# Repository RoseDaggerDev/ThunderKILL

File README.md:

# ThunderKILL

ThunderKILL is based on the [Thundervolt](https://github.com/mackieks/thundervolt/tree/main) by [YveltalGriffin](https://github.com/mackieks) an open source platform for undervolting the Nintendo Wiis.
ThunderKILL takes the original concept and tries to go overkill with more features explicitly not inculded in the Thundervolt.
### New features:
- USB-C Power delivery
- Battery charge controller
- Fan and temperature controller
- RGB LED controller
- Current sensing
- 5V boost regulator
- E-Fuse on the PD power in
- Resettable fuse on the battery connection

### Existing features from Thundervolt:
- 1V buck regulator
- 1.15V buck regulator
- 1.8V buck regulator
- 3.3V buck boost regulator

All regulators are I2C controlled and high efficiency (η > 90%) and can be(/will be) controllable from a homebrew app. Along with the data from the I2C current/voltage/power sensing and temperature sensing of the board and the Wii.
The ThunderKILL has significantly more output pads than the original Thundervolt, as it is designed to integrate with other boards beyond the Wii itself, supplying easily available power, along with all the new features like PD negotiation, fan and LED outputs.

### ToDo:
- Final pass on board
- Send to printing
- Solder components
- Develop firmware
- Test in isolation
- Test on Wii
- Develop homebrew app

### NOTE: ThunderKILL is still in the prototype phase, and is untested, and the firmware for it has yet to be developed. I don’t recommend manufacturing ThunderKILL PCBs until development and testing are complete. This project is currently only for reference.

(This github page is still WIP, and will change as the project continues)

## Screenshots

## Credits

ThunderKILL hardware designed by [RoseDaggerDev](https://github.com/RoseDaggerDev)

Original Thundervolt credits:

Thundervolt hardware designed by [YveltalGriffin](https://github.com/mackieks)

Thundervolt firmware by [loopj ](https://github.com/loopj)

Thundervolt homebrew by:
- [YveltalGriffin](https://github.com/mackieks) (UI, app)
-  [loopj ](https://github.com/loopj) (I2C, app)
-  [Alex/supertazon](https://github.com/supertazon) (graphics)
-  [ShockSlayer ](https://github.com/ShockSlayer) (music)

## License

ThunderKILL hardware is licensed under Solderpad Hardware License v2.1.

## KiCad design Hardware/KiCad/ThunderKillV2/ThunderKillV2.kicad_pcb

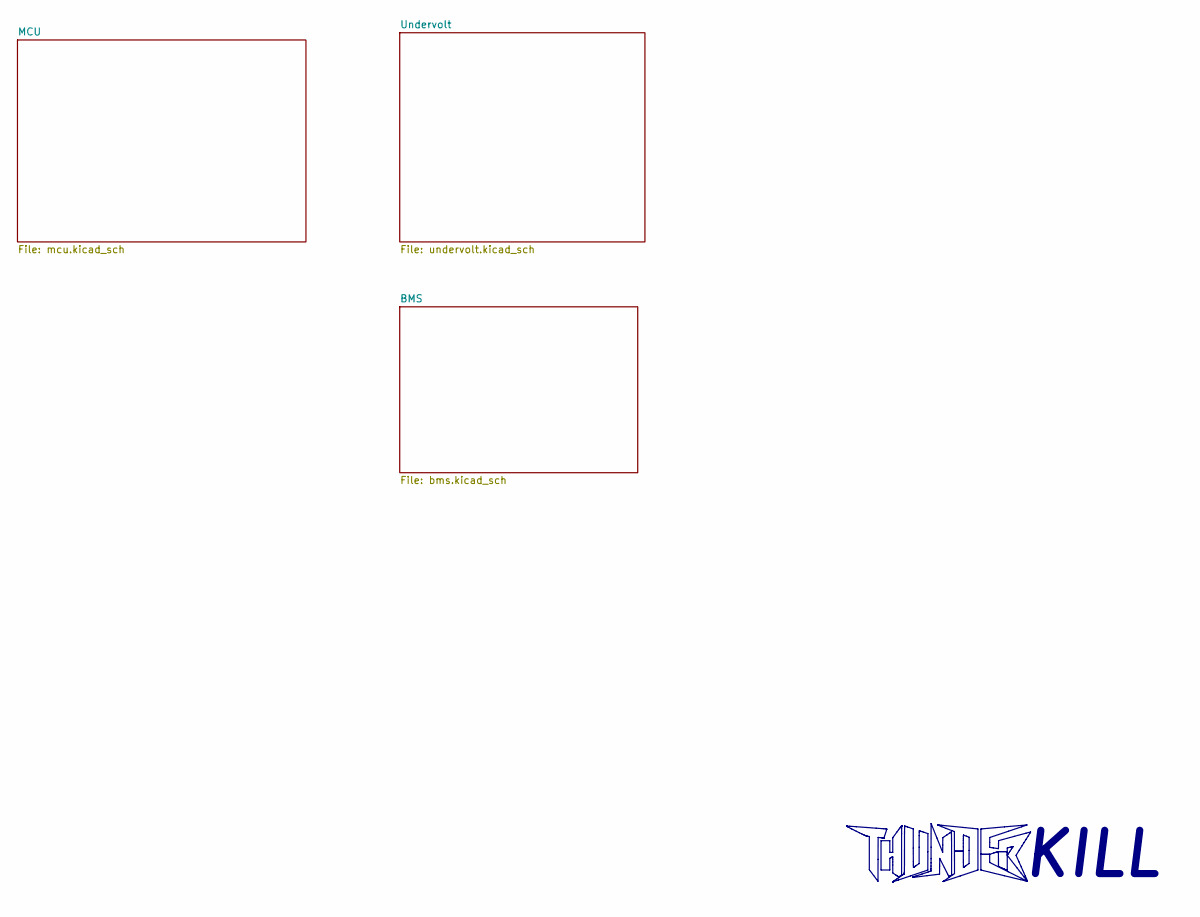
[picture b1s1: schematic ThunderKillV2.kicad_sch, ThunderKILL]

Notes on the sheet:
KILL

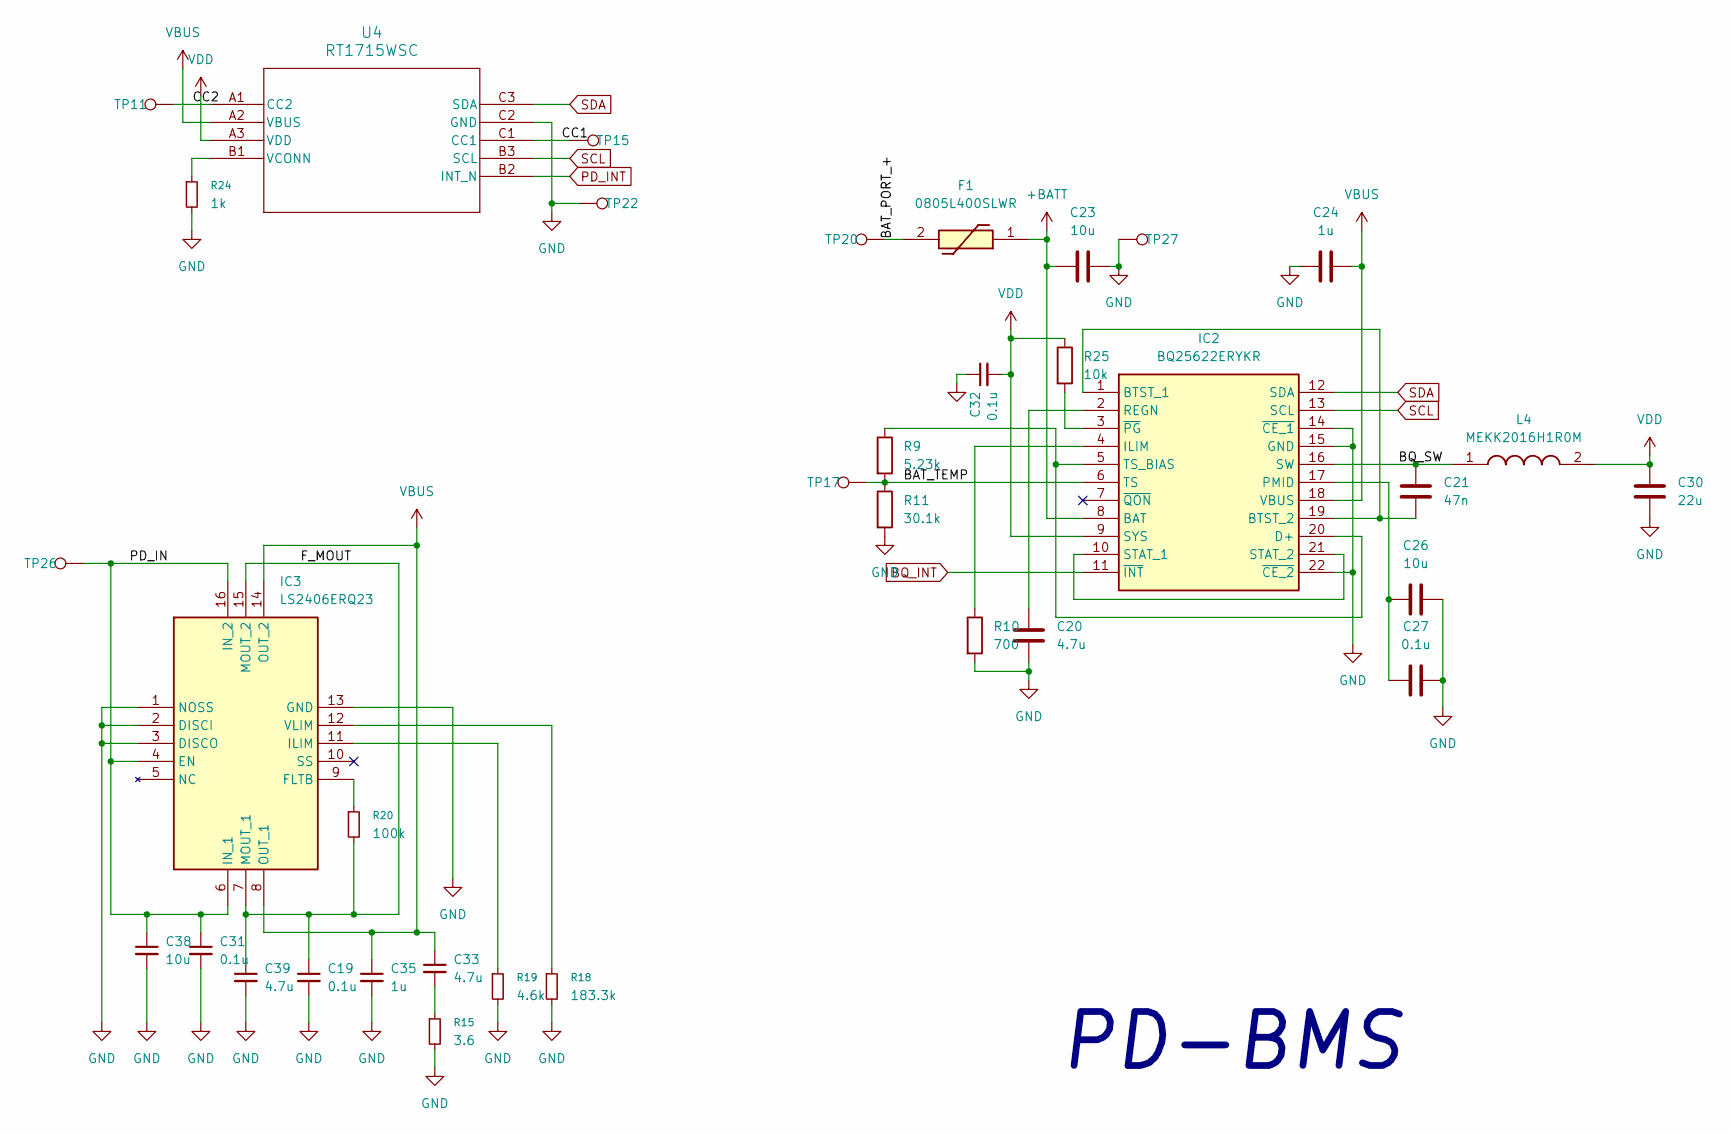
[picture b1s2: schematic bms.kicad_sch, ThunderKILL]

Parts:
C19, C27, C31, C32: 0.1u; C_0402_1005Metric; Manufacturer_Part_Number GCM155R71H104KE02J; Digi-Key Part # 490-14514-1-ND
C20, C33, C39: 4.7u; C_0402_1005Metric; Manufacturer_Part_Number GRM155C61E475ME15J; Digi-Key Part # 490-GRM155C61E475ME15JCT-ND
C21: 47n; C_0402_1005Metric; Manufacturer_Part_Number GRM155R71H473KE14D; Digi-Key Part # 490-10702-1-ND
C23, C26, C38: 10u; C_0603_1608Metric; Manufacturer_Part_Number GRM188R61E106KA73D; Digi-Key Part # 490-18214-1-ND
C24, C35: 1u; C_0402_1005Metric; Manufacturer_Part_Number GRM155R61E105KA12D; Digi-Key Part # 490-10017-1-ND
C30: 22u; C_0603_1608Metric; Manufacturer_Part_Number GRM188C61E226ME01W; Digi-Key Part # 490-GRM188C61E226ME01WCT-ND
F1: 0805L400SLWR; 0805L075SLYR; Mouser Part Number 576-0805L400SLWR
IC2: BQ25622ERYKR; Mouser Part Number 595-BQ25622ERYKR
IC3: LS2406ERQ23; Mouser Part Number 576-LS2406ERQ23
L4: MEKK2016H1R0M; INDPM2016X100N; Mouser Part Number 963-MEKK2016H1R0M
R9: 5.23k; R_0402_1005Metric; Manufacturer_Part_Number RMCF0402FT5K23; Digi-Key Part # RMCF0402FT5K23CT-ND
R10: 700; R_0402_1005Metric; Manufacturer_Part_Number RMCF0402FT698R; Digi-Key Part # RMCF0402FT698RCT-ND
R11: 30.1k; R_0402_1005Metric; Manufacturer_Part_Number RMCF0402FT30K1; Digi-Key Part # RMCF0402FT30K1CT-ND
R15: 3.6; R_0402_1005Metric; Manufacturer_Part_Number RMCF0402FT3R60; Digi-Key Part # RMCF0402FT3R60CT-ND
R18: 183.3k; R_0402_1005Metric; Manufacturer_Part_Number RMCF0402FT182K; Digi-Key Part # RMCF0402FT182KCT-ND
R19: 4.6k; R_0402_1005Metric; Manufacturer_Part_Number RMCF0402FT4K64; Digi-Key Part # RMCF0402FT4K64CT-ND
R20: 100k; R_0402_1005Metric; Manufacturer_Part_Number CRCW0402100KFKED; Digi-Key Part # 541-100KLCT-ND
R24: 1k; R_0402_1005Metric; Manufacturer_Part_Number CRCW04021K00FKED; Digi-Key Part # 541-1.00KLCT-ND
R25: 10k; R_0402_1005Metric; Manufacturer_Part_Number CRCW040210K0FKED; Digi-Key Part # 541-10.0KLCT-ND
TP11: CC2; TestPoint_Pad_D1.0mm
TP15: CC1; TestPoint_Pad_D1.0mm
TP17: BAT_TMP; TestPoint_Pad_D1.0mm
TP20: BAT+; TestPoint_Pad_3x1.0mm
TP22: GND; TestPoint_Pad_3x1.0mm
TP26: VBUS; TestPoint_Pad_3x1.0mm
TP27: BAT-; TestPoint_Pad_3x1.0mm
U4: RT1715WSC; BGA3X3_RT1715WSC_RIT; Manufacturer_Part_Number RT1715WSC; Digi-Key Part # RT1715WSCCT-ND

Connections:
+BATT: C23.1, F1.1, IC2.8 (BAT)
/BMS/BAT_PORT_+: F1.2, TP20.1
/BMS/BAT_TEMP: IC2.6 (TS), R9.2, R11.1, TP17.1
/BMS/BQ_SW: C21.1, IC2.16 (SW), L4.1
/BMS/CC1: TP15.1, U4.C1 (CC1)
/BMS/CC2: TP11.1, U4.A1 (CC2)
/BMS/F_MOUT: C19.1, C39.1, IC3.7 (MOUT_1), IC3.15 (MOUT_2), R20.2
/BMS/PD_IN: C31.1, C38.1, IC3.4 (EN), IC3.6 (IN_1), IC3.16 (IN_2), TP26.1
BQ_INT: IC2.11 (~INT); also elsewhere on the board
GND: C19.2, C20.2, C23.2, C24.1, C26.2, C27.2, C30.2, C31.2, C32.1, C35.2, C38.2, C39.2, IC2.14 (~CE_1), IC2.15 (GND), IC2.22 (~CE_2), IC3.1 (NOSS), IC3.2 (DISCI), IC3.3 (DISCO), IC3.13 (GND), R10.2, R11.2, R15.2, R18.2, R19.2, R24.2, TP22.1, TP27.1, U4.C2 (GND); also elsewhere on the board
unnamed: C33.2, R15.1
unnamed: C21.2, IC2.1 (BTST_1), IC2.19 (BTST_2)
unnamed: IC2.5 (TS_BIAS), IC2.20 (D+), R9.1
unnamed: IC2.4 (ILIM), R10.1
unnamed: C26.1, C27.1, IC2.17 (PMID)
unnamed: C20.1, IC2.2 (REGN)
unnamed: IC2.10 (STAT_1), IC2.21 (STAT_2)
unnamed: IC2.3 (~PG), R25.2
unnamed: IC3.9 (FLTB), R20.1
unnamed: IC3.11 (ILIM), R19.1
unnamed: IC3.12 (VLIM), R18.1
unnamed: R24.1, U4.B1 (VCONN)
PD_INT: U4.B2 (INT_N); also elsewhere on the board
SCL: IC2.13 (SCL), U4.B3 (SCL); also elsewhere on the board
SDA: IC2.12 (SDA), U4.C3 (SDA); also elsewhere on the board
VBUS: C24.2, C33.1, C35.1, IC2.18 (VBUS), IC3.8 (OUT_1), IC3.14 (OUT_2), U4.A2 (VBUS)
VDD: C30.1, C32.2, IC2.9 (SYS), L4.2, R25.1, U4.A3 (VDD); also elsewhere on the board

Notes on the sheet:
PD-BMS

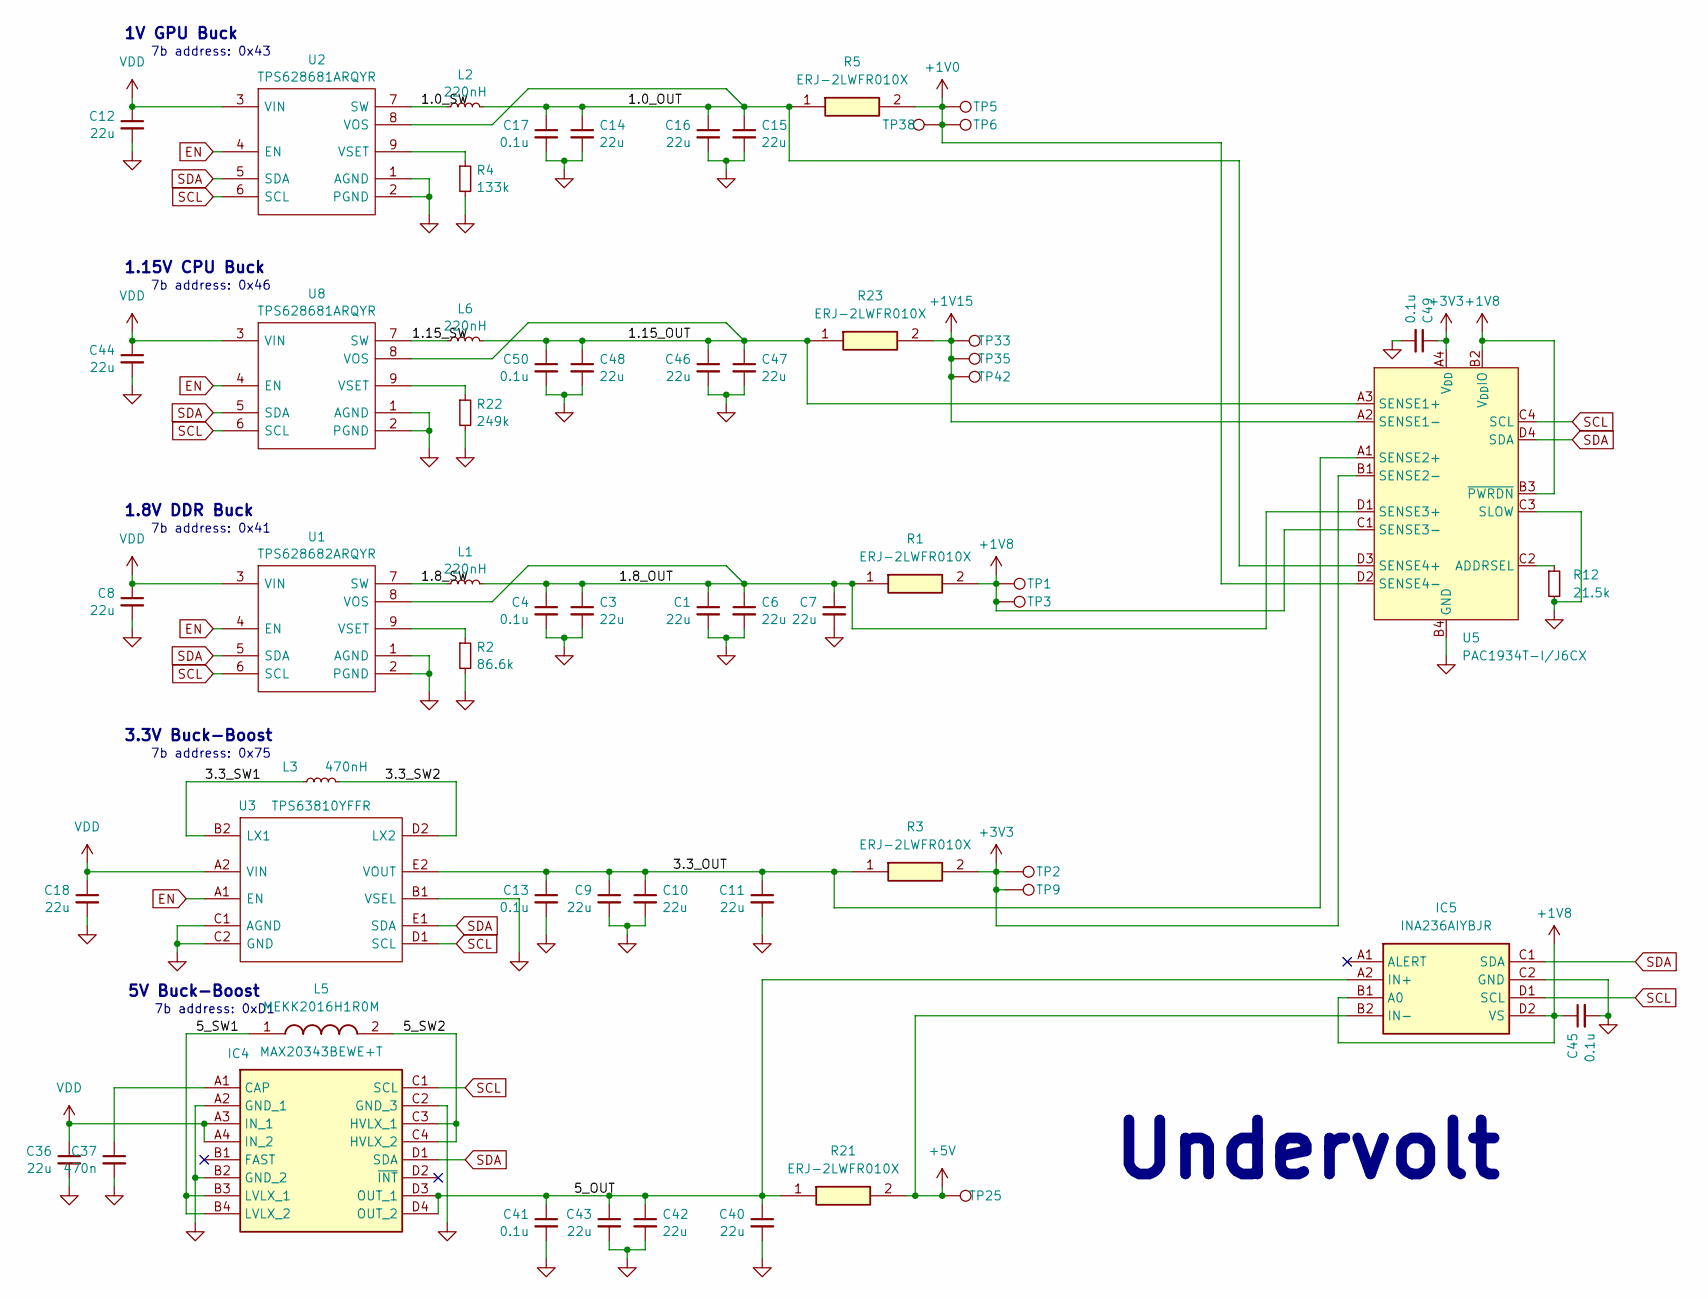
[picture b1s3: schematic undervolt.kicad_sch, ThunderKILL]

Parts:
C1, C3, C6, C7, C8, C9, C10, C11, C12, C14, C15, C16, C18, C36, C40, C42, C43, C44, C46, C47, C48: 22u; C_0603_1608Metric; Manufacturer_Part_Number GRM188C61E226ME01W; Digi-Key Part # 490-GRM188C61E226ME01WCT-ND
C4, C13, C17, C41, C45, C49, C50: 0.1u; C_0402_1005Metric; Manufacturer_Part_Number GCM155R71H104KE02J; Digi-Key Part # 490-14514-1-ND
C37: 470n; C_0402_1005Metric; Manufacturer_Part_Number GRM155R61E105KA12D; Digi-Key Part # 490-10017-1-ND
IC4: MAX20343BEWE+T; BGA16C40P4X4_201X177X69; Mouser Part Number 700-MAX20343BEWE+T
IC5: INA236AIYBJR; BGA8C40P2X4_70X147X35; Mouser Part Number 595-INA236AIYBJR
L1, L2, L6: 220nH; INDPM4442X150N; Manufacturer_Part_Number MPI4015V2-R22-R; Digi-Key Part # 283-MPI4015V2-R22-RCT-ND
L3: 470nH; L_0805_2012Metric; Manufacturer_Part_Number TFM201208BLE-R47MTCF; Digi-Key Part # 445-TFM201208BLE-R47MTCFCT-ND
L5: MEKK2016H1R0M; INDPM2016X100N; Mouser Part Number 963-MEKK2016H1R0M
R1, R3, R5, R21, R23: ERJ-2LWFR010X; R_0402_1005Metric; Mouser Part Number 667-ERJ-2LWFR010X
R2: 86.6k; R_0402_1005Metric; Manufacturer_Part_Number RMCF0402FT86K6; Digi-Key Part # RMCF0402FT86K6CT-ND
R4: 133k; R_0402_1005Metric; Manufacturer_Part_Number RMCF0402FT133K; Digi-Key Part # RMCF0402FT133KCT-ND
R12: 21.5k; R_0402_1005Metric; Manufacturer_Part_Number RMCF0402FT3R60; Digi-Key Part # RMCF0402FT3R60CT-ND
R22: 249k; R_0402_1005Metric; Manufacturer_Part_Number CRCW0402249KFKED; Digi-Key Part # 541-249KLCT-ND
TP1, TP3: 1V8; TestPoint_Pad_3x1.0mm
TP2: 3V3; TestPoint_Pad_1.5x1.0mm
TP5, TP6, TP38: 1V0; TestPoint_Pad_3x1.0mm
TP9: 3V3; TestPoint_Pad_3x1.0mm
TP25: 5V; TestPoint_Pad_3x1.0mm
TP33, TP35, TP42: 1V15; TestPoint_Pad_3x1.0mm
U1: TPS628682ARQYR; TPS628680ARQYR; Mouser Part Number 595-TPS628682ARQYR
U2, U8: TPS628681ARQYR; TPS628680ARQYR; Mouser Part Number 595-TPS628681ARQYR
U3: TPS63810YFFR; BGA15C40P3X5_134X226X62; Mouser Part Number 595-TPS63810YFFR
U5: PAC1934T-I/J6CX; WLCSP-16_2.225x2.17mm_Layout4x4_P0.5mm; Manufacturer_Part_Number PAC1934T-I/J6CX; Digi-Key Part # PAC1934T-I/J6CX-CT-ND

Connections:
+1V0: R5.2, TP5.1, TP6.1, TP38.1, U5.D2 (SENSE4-)
+1V8: C45.1, IC5.B1 (A0), IC5.D2 (VS), R1.2, TP1.1, TP3.1, U5.B2 (V_{DD}IO), U5.B3 (~PWRDN), U5.C1 (SENSE3-); also elsewhere on the board
+1V15: R23.2, TP33.1, TP35.1, TP42.1, U5.A2 (SENSE1-)
+3V3: C49.1, R3.2, TP2.1, TP9.1, U5.A4 (V_{DD}), U5.B1 (SENSE2-); also elsewhere on the board
+5V: IC5.B2 (IN-), R21.2, TP25.1
/Undervolt/1.0_OUT: C14.1, C15.1, C16.1, C17.1, L2.2, R5.1, U2.8 (VOS), U5.D3 (SENSE4+)
/Undervolt/1.0_SW: L2.1, U2.7 (SW)
/Undervolt/1.8_OUT: C1.1, C3.1, C4.1, C6.1, C7.1, L1.2, R1.1, U1.8 (VOS), U5.D1 (SENSE3+)
/Undervolt/1.8_SW: L1.1, U1.7 (SW)
/Undervolt/1.15_OUT: C46.1, C47.1, C48.1, C50.1, L6.2, R23.1, U5.A3 (SENSE1+), U8.8 (VOS)
/Undervolt/1.15_SW: L6.1, U8.7 (SW)
/Undervolt/3.3_OUT: C9.1, C10.1, C11.1, C13.1, R3.1, U3.E2 (VOUT), U3.E3 (VOUT_2), U5.A1 (SENSE2+)
/Undervolt/3.3_SW1: L3.1, U3.B2 (LX1), U3.B3 (LX1_2)
/Undervolt/3.3_SW2: L3.2, U3.D2 (LX2), U3.D3 (LX2_2)
/Undervolt/5_OUT: C40.1, C41.1, C42.1, C43.1, IC4.D3 (OUT_1), IC4.D4 (OUT_2), IC5.A2 (IN+), R21.1
/Undervolt/5_SW1: IC4.B3 (LVLX_1), IC4.B4 (LVLX_2), L5.1
/Undervolt/5_SW2: IC4.C3 (HVLX_1), IC4.C4 (HVLX_2), L5.2
EN: U1.4 (EN), U2.4 (EN), U3.A1 (EN), U8.4 (EN); also elsewhere on the board
GND: C1.2, C3.2, C4.2, C6.2, C7.2, C8.2, C9.2, C10.2, C11.2, C12.2, C13.2, C14.2, C15.2, C16.2, C17.2, C18.2, C36.2, C37.2, C40.2, C41.2, C42.2, C43.2, C44.2, C45.2, C46.2, C47.2, C48.2, C49.2, C50.2, IC4.A2 (GND_1), IC4.B2 (GND_2), IC4.C2 (GND_3), IC5.C2 (GND), R2.2, R4.2, R12.2, R22.2, U1.1 (AGND), U1.2 (PGND), U2.1 (AGND), U2.2 (PGND), U3.B1 (VSEL), U3.C1 (AGND), U3.C2 (GND), U3.C3 (GND_2), U5.B4 (GND), U5.C3 (SLOW), U8.1 (AGND), U8.2 (PGND); also elsewhere on the board
unnamed: C37.1, IC4.A1 (CAP)
unnamed: R2.1, U1.9 (VSET)
unnamed: R4.1, U2.9 (VSET)
unnamed: R12.1, U5.C2 (ADDRSEL)
unnamed: R22.1, U8.9 (VSET)
SCL: IC4.C1 (SCL), IC5.D1 (SCL), U1.6 (SCL), U2.6 (SCL), U3.D1 (SCL), U5.C4 (SCL), U8.6 (SCL); also elsewhere on the board
SDA: IC4.D1 (SDA), IC5.C1 (SDA), U1.5 (SDA), U2.5 (SDA), U3.E1 (SDA), U5.D4 (SDA), U8.5 (SDA); also elsewhere on the board
VDD: C8.1, C12.1, C18.1, C36.1, C44.1, IC4.A3 (IN_1), IC4.A4 (IN_2), U1.3 (VIN), U2.3 (VIN), U3.A2 (VIN), U3.A3 (VIN_2), U8.3 (VIN); also elsewhere on the board

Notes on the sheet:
1.8V DDR Buck
7b address: 0x75
3.3V Buck-Boost
1.15V CPU Buck
7b address: 0x43
7b address: 0xD1
7b address: 0x41
1V GPU Buck
Undervolt
5V Buck-Boost
7b address: 0x46

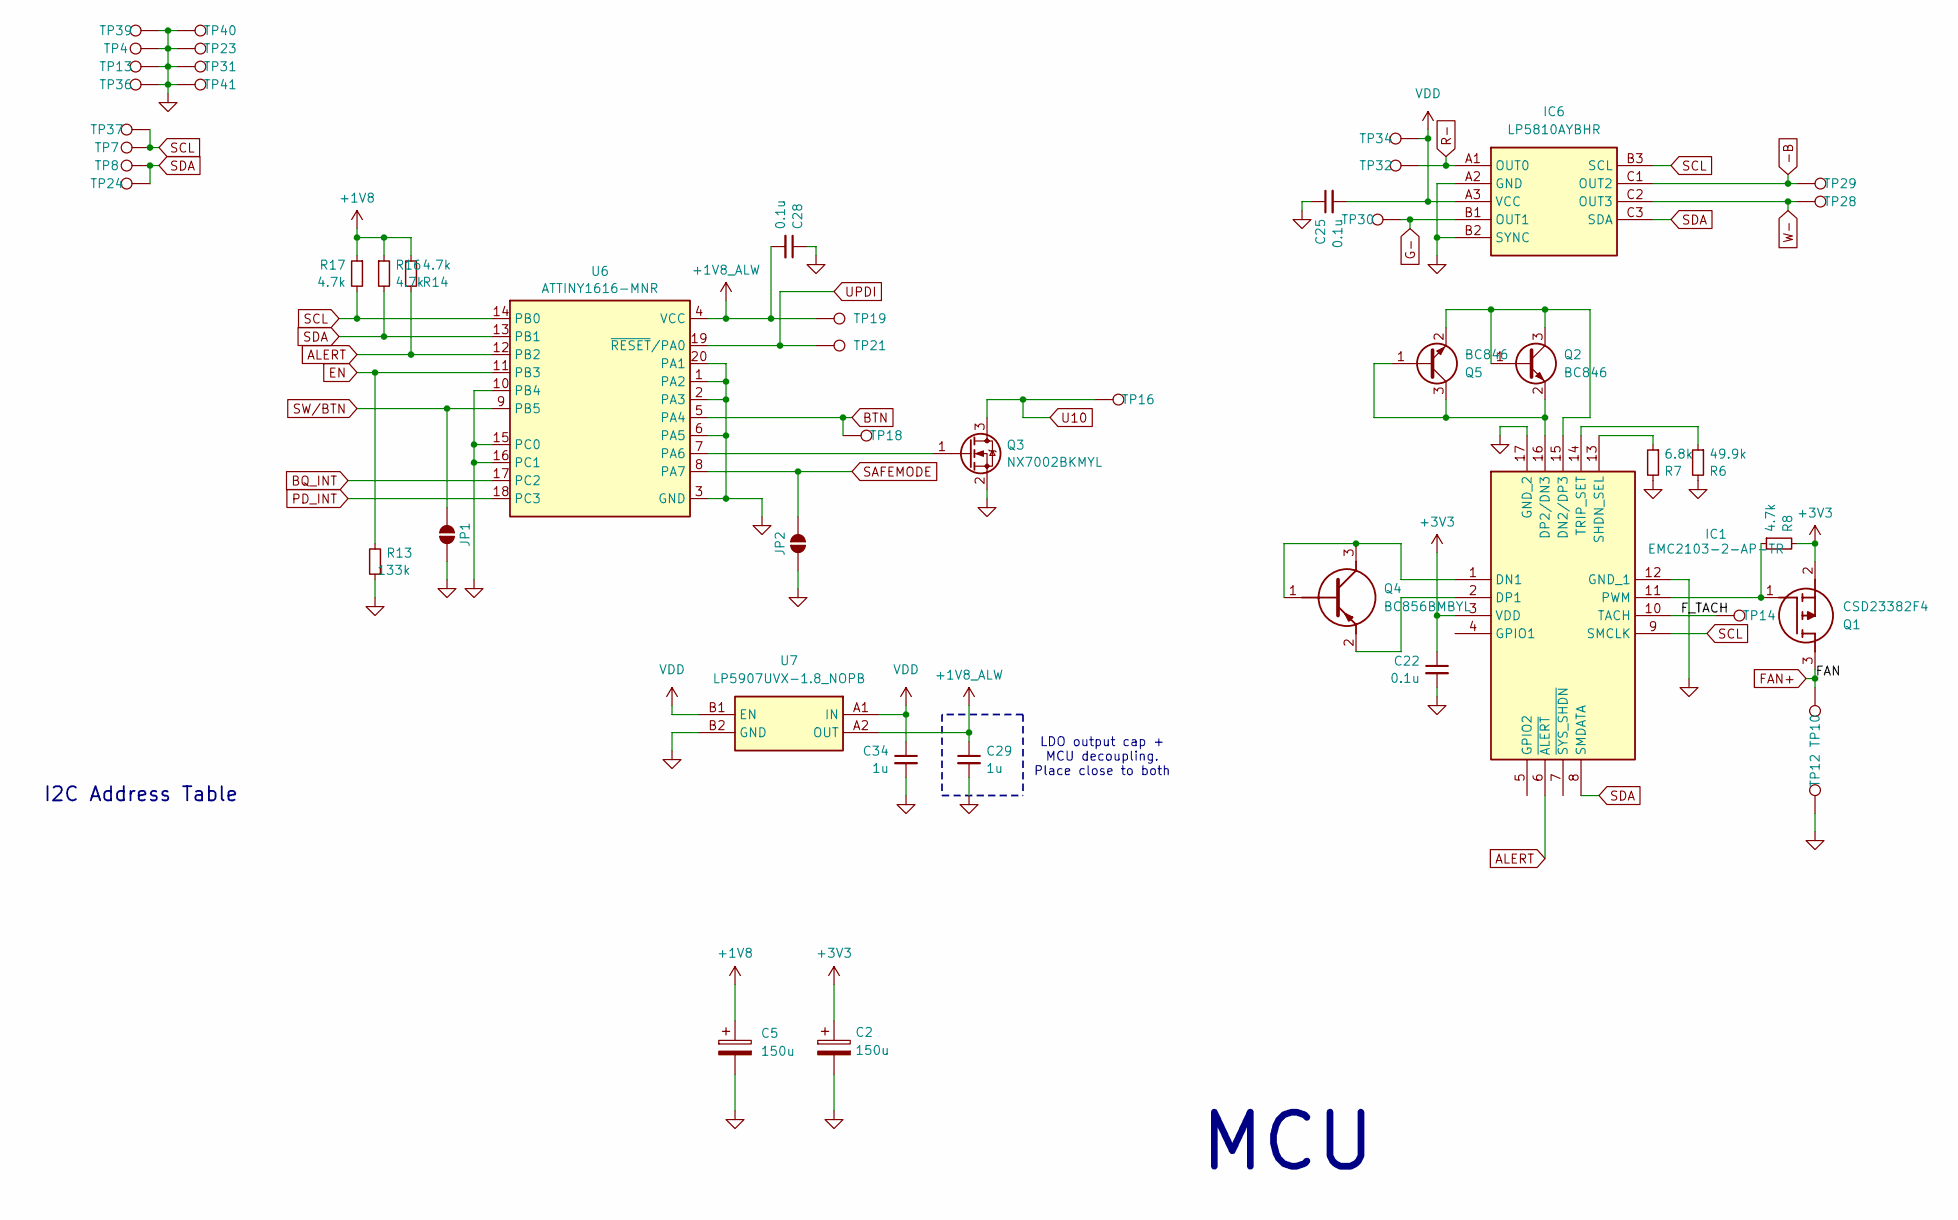
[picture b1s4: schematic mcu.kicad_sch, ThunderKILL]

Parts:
C2, C5: 150u; CP_EIA-3528-15_AVX-H; Manufacturer_Part_Number 6TPS150MUD; Digi-Key Part # 10-6TPS150MUDCT-ND
C22, C25, C28: 0.1u; C_0402_1005Metric; Manufacturer_Part_Number GCM155R71H104KE02J; Digi-Key Part # 490-14514-1-ND
C29, C34: 1u; C_0402_1005Metric; Manufacturer_Part_Number GRM155R61E105KA12D; Digi-Key Part # 490-10017-1-ND
IC1: EMC2103-2-AP-TR; EMC21032APTR; Mouser Part Number 886-EMC2103-2-AP-TR
IC6: LP5810AYBHR; BGA9C40P3X3_143X134X40; Mouser Part Number 595-LP5810AYBHR
JP1, JP2: SolderJumper_2_Open; SolderJumper-2_P1.3mm_Open_RoundedPad1.0x1.5mm
Q1: CSD23382F4; YJC; Mouser Part Number 595-CSD23382F4
Q2: BC846; SOT-23; Manufacturer_Part_Number BC846B-7-F; Digi-Key Part # BC846B-FDICT-ND
Q3: NX7002BKMYL; Diodes_DFN1006-3; Manufacturer_Part_Number NX7002BKMYL; Digi-Key Part # 1727-2232-1-ND
Q4: BC856BMBYL; Mouser Part Number 771-BC856BMBYL
Q5: BC846; BC856BMBYL; Manufacturer_Part_Number BC846BLP4-7B; Digi-Key Part # BC846BLP4-7BDICT-ND
R6: 49.9k; R_0402_1005Metric; Manufacturer_Part_Number RMCF0402FT49K9; Digi-Key Part # RMCF0402FT49K9CT-ND
R7: 6.8k; R_0402_1005Metric; Manufacturer_Part_Number RMCF0402FT6K80; Digi-Key Part # RMCF0402FT6K80
R8, R14, R16, R17: 4.7k; R_0402_1005Metric; Manufacturer_Part_Number RMCF0402FT4K70; Digi-Key Part # RMCF0402FT4K70CT-ND
R13: 133k; R_0402_1005Metric; Manufacturer_Part_Number RMCF0402FT133K; Digi-Key Part # RMCF0402FT133KCT-ND
TP4, TP13, TP31, TP36, TP39, TP40, TP41: GND; TestPoint_Pad_3x1.0mm
TP7, TP37: SCL; TestPoint_Pad_D1.0mm
TP8, TP24: SDA; TestPoint_Pad_D1.0mm
TP10: FAN+; TestPoint_Pad_D1.0mm
TP12: FAN-; TestPoint_Pad_D1.0mm
TP14: FAN_TACH; TestPoint_Pad_D1.0mm
TP16, TP23: U10; TestPoint_Pad_D1.0mm
TP18: BTN; TestPoint_Pad_D1.0mm
TP19: VBAT; TestPoint_Pad_D1.0mm
TP21: UPDI; TestPoint_Pad_D1.0mm
TP28: LED -W; TestPoint_Pad_D1.0mm
TP29: LED -B; TestPoint_Pad_D1.0mm
TP30: LED -G; TestPoint_Pad_D1.0mm
TP32: LED -R; TestPoint_Pad_D1.0mm
TP34: LED +; TestPoint_Pad_D1.0mm
U6: ATTINY1616-MNR; VQFN-20-1EP_3x3mm_P0.4mm_EP1.7x1.7mm; Manufacturer_Part_Number ATTINY1616-MNR; Digi-Key Part # ATTINY1616-MNRCT-ND
U7: LP5907UVX-1.8_NOPB; BGA4C35P2X2_64X64X44; Mouser Part Number 926-LP5907UVX1.8NOPB

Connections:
+1V8: C5.1, R14.2, R16.1, R17.1; also elsewhere on the board
+1V8_ALW: C28.2, C29.1, TP19.1, U6.4 (VCC), U7.A2 (OUT)
+3V3: C2.1, C22.1, IC1.3 (VDD), Q1.2 (S), R8.2; also elsewhere on the board
-B: IC6.C1 (OUT2), TP29.1
/MCU/F_TACH: IC1.10 (TACH), TP14.1
ALERT: IC1.6 (~ALERT), R14.1, U6.12 (PB2)
BQ_INT: U6.17 (PC2); also elsewhere on the board
BTN: TP18.1, U6.5 (PA4)
EN: R13.2, U6.11 (PB3); also elsewhere on the board
FAN+: Q1.3 (D), TP10.1
G-: IC6.B1 (OUT1), TP30.1
GND: C2.2, C5.2, C22.2, C25.1, C28.1, C29.2, C34.2, IC1.12 (GND_1), IC1.17 (GND_2), IC6.A2 (GND), IC6.B2 (SYNC), JP1.1 (A), JP2.1 (A), Q3.2 (S), R6.2, R7.2, R13.1, TP4.1, TP12.1, TP13.1, TP23.1, TP31.1, TP36.1, TP39.1, TP40.1, TP41.1, U6.1 (PA2), U6.2 (PA3), U6.3 (GND), U6.6 (PA5), U6.10 (PB4), U6.15 (PC0), U6.16 (PC1), U6.20 (PA1), U6.21 (GND), U7.B2 (GND); also elsewhere on the board
unnamed: IC1.1 (DN1), Q4.1 (B), Q4.3 (C)
unnamed: IC1.15 (DN2/DP3), Q2.1 (B), Q2.3 (C), Q5.2 (E)
unnamed: IC1.2 (DP1), Q4.2 (E)
unnamed: IC1.16 (DP2/DN3), Q2.2 (E), Q5.1 (B), Q5.3 (C)
unnamed: IC1.11 (PWM), Q1.1 (G), R8.1
unnamed: IC1.13 (SHDN_SEL), R7.1
unnamed: IC1.14 (TRIP_SET), R6.1
unnamed: Q3.1 (G), U6.7 (PA6)
PD_INT: U6.18 (PC3); also elsewhere on the board
R-: IC6.A1 (OUT0), TP32.1
SAFEMODE: JP2.2 (B), U6.8 (PA7)
SCL: IC1.9 (SMCLK), IC6.B3 (SCL), R17.2, TP7.1, TP37.1, U6.14 (PB0); also elsewhere on the board
SDA: IC1.8 (SMDATA), IC6.C3 (SDA), R16.2, TP8.1, TP24.1, U6.13 (PB1); also elsewhere on the board
SW/BTN: JP1.2 (B), U6.9 (PB5)
U10: Q3.3 (D), TP16.1
UPDI: TP21.1, U6.19 (~RESET/PA0)
VDD: C25.2, C34.1, IC6.A3 (VCC), TP34.1, U7.A1 (IN), U7.B1 (EN); also elsewhere on the board
W-: IC6.C2 (OUT3), TP28.1

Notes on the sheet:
I2C Address Table
MCU
LDO output cap + MCU decoupling. Place close to both

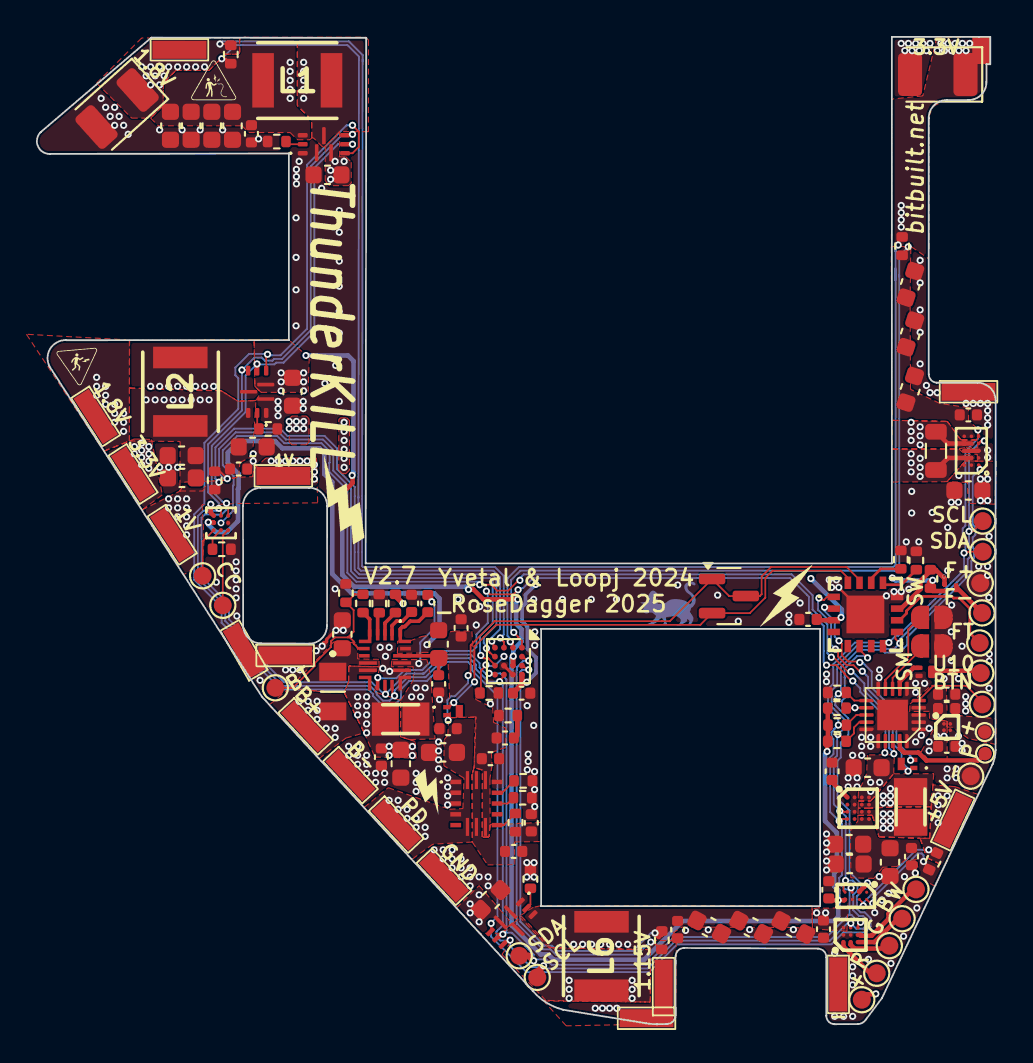
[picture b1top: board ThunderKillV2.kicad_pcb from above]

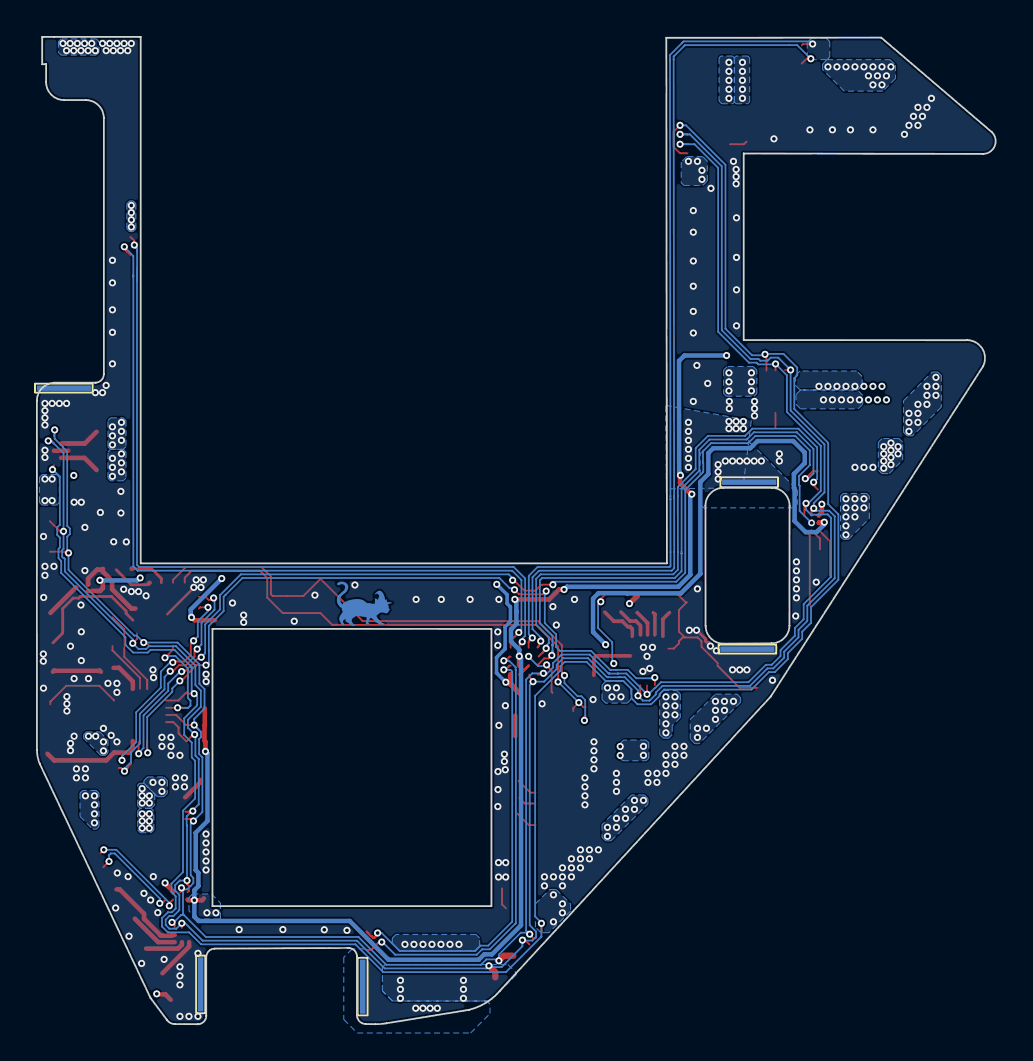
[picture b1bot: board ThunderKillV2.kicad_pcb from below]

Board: 4 copper layers, 53.3 x 54.8 mm, 145 parts (5 on the bottom side), 71 nets.

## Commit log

2025-09-04 Updated thunderkill to V2 near production ready
2025-09-05 Updated to fix 3d file paths, and updated page settings with version number and author.
    Also updated the name for ThunderKILL V1
2025-09-05 Added images and updated README
2025-09-05 Update README.md
    Adjusted images in readme
2025-09-05 Update README.md
    Rereadjusted images
2025-09-05 Update README.md
    Made images bigger again
2025-09-05 Update README.md
    Final update to clean up read me text, and adding todo section
2026-06-22 Updating to newest local version
